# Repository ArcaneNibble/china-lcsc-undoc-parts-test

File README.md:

# China / LCSC poorly-documented parts tester PCB

## TM8211

This is a cheap I2S DAC that looks like it is intended for set-top-boxes. Allegedly, there is no minium clock speed. The goal is to determine if this is indeed true, in which case it can be bit-banged instead of doing proper I2S with a continuously-running clock. If it were to be the case, we would want to know the output impedance of the DAC.

### Status

I haven't managed to get this chip to output anything at all so far, even with a continuous clock. Further investigation needed.

## EA3058

This is a 4-channel buck converter. I wanted to characterize its performance in more detail than the few graphs in the datasheet.

### Status

The zero-load performance seems quite poor on the 1.2 V output. Further measurements have not been made yet.

## LGS5500

This is a LiPo charger and boost converter with automagic power path / load sharing. It appears to be perfectly-suited for battery-powered "maker" projects, especially ones that need 5 V and/or want to be able to push batteries to ~3 V rather than ~3.4 V (with an ultra-low-dropout regulator) or even higher voltages (using less and less of the battery capacity). Once again I wanted to characterize the performance in more detail than in the datasheet.

### Status

There is somewhat undesired behavior if there is no battery connected. Automagic power path / load sharing appears to work very well, but more measurements need to be made of whether spikes/dips happen. Needs more testing of the boost converter under load.

## APW7261

This is another LiPo charger and boost converter that is especially cheap. It was a bit unclear how (in)convenient it would be to use. It was also a test of using WLCSPs and pushing JLCPCB minimums.

### Status

This is clearly designed for legacy OTG, and it doesn't have the same type of automagic power path / load sharing as the previous part. It was assembled successfully without any issues.

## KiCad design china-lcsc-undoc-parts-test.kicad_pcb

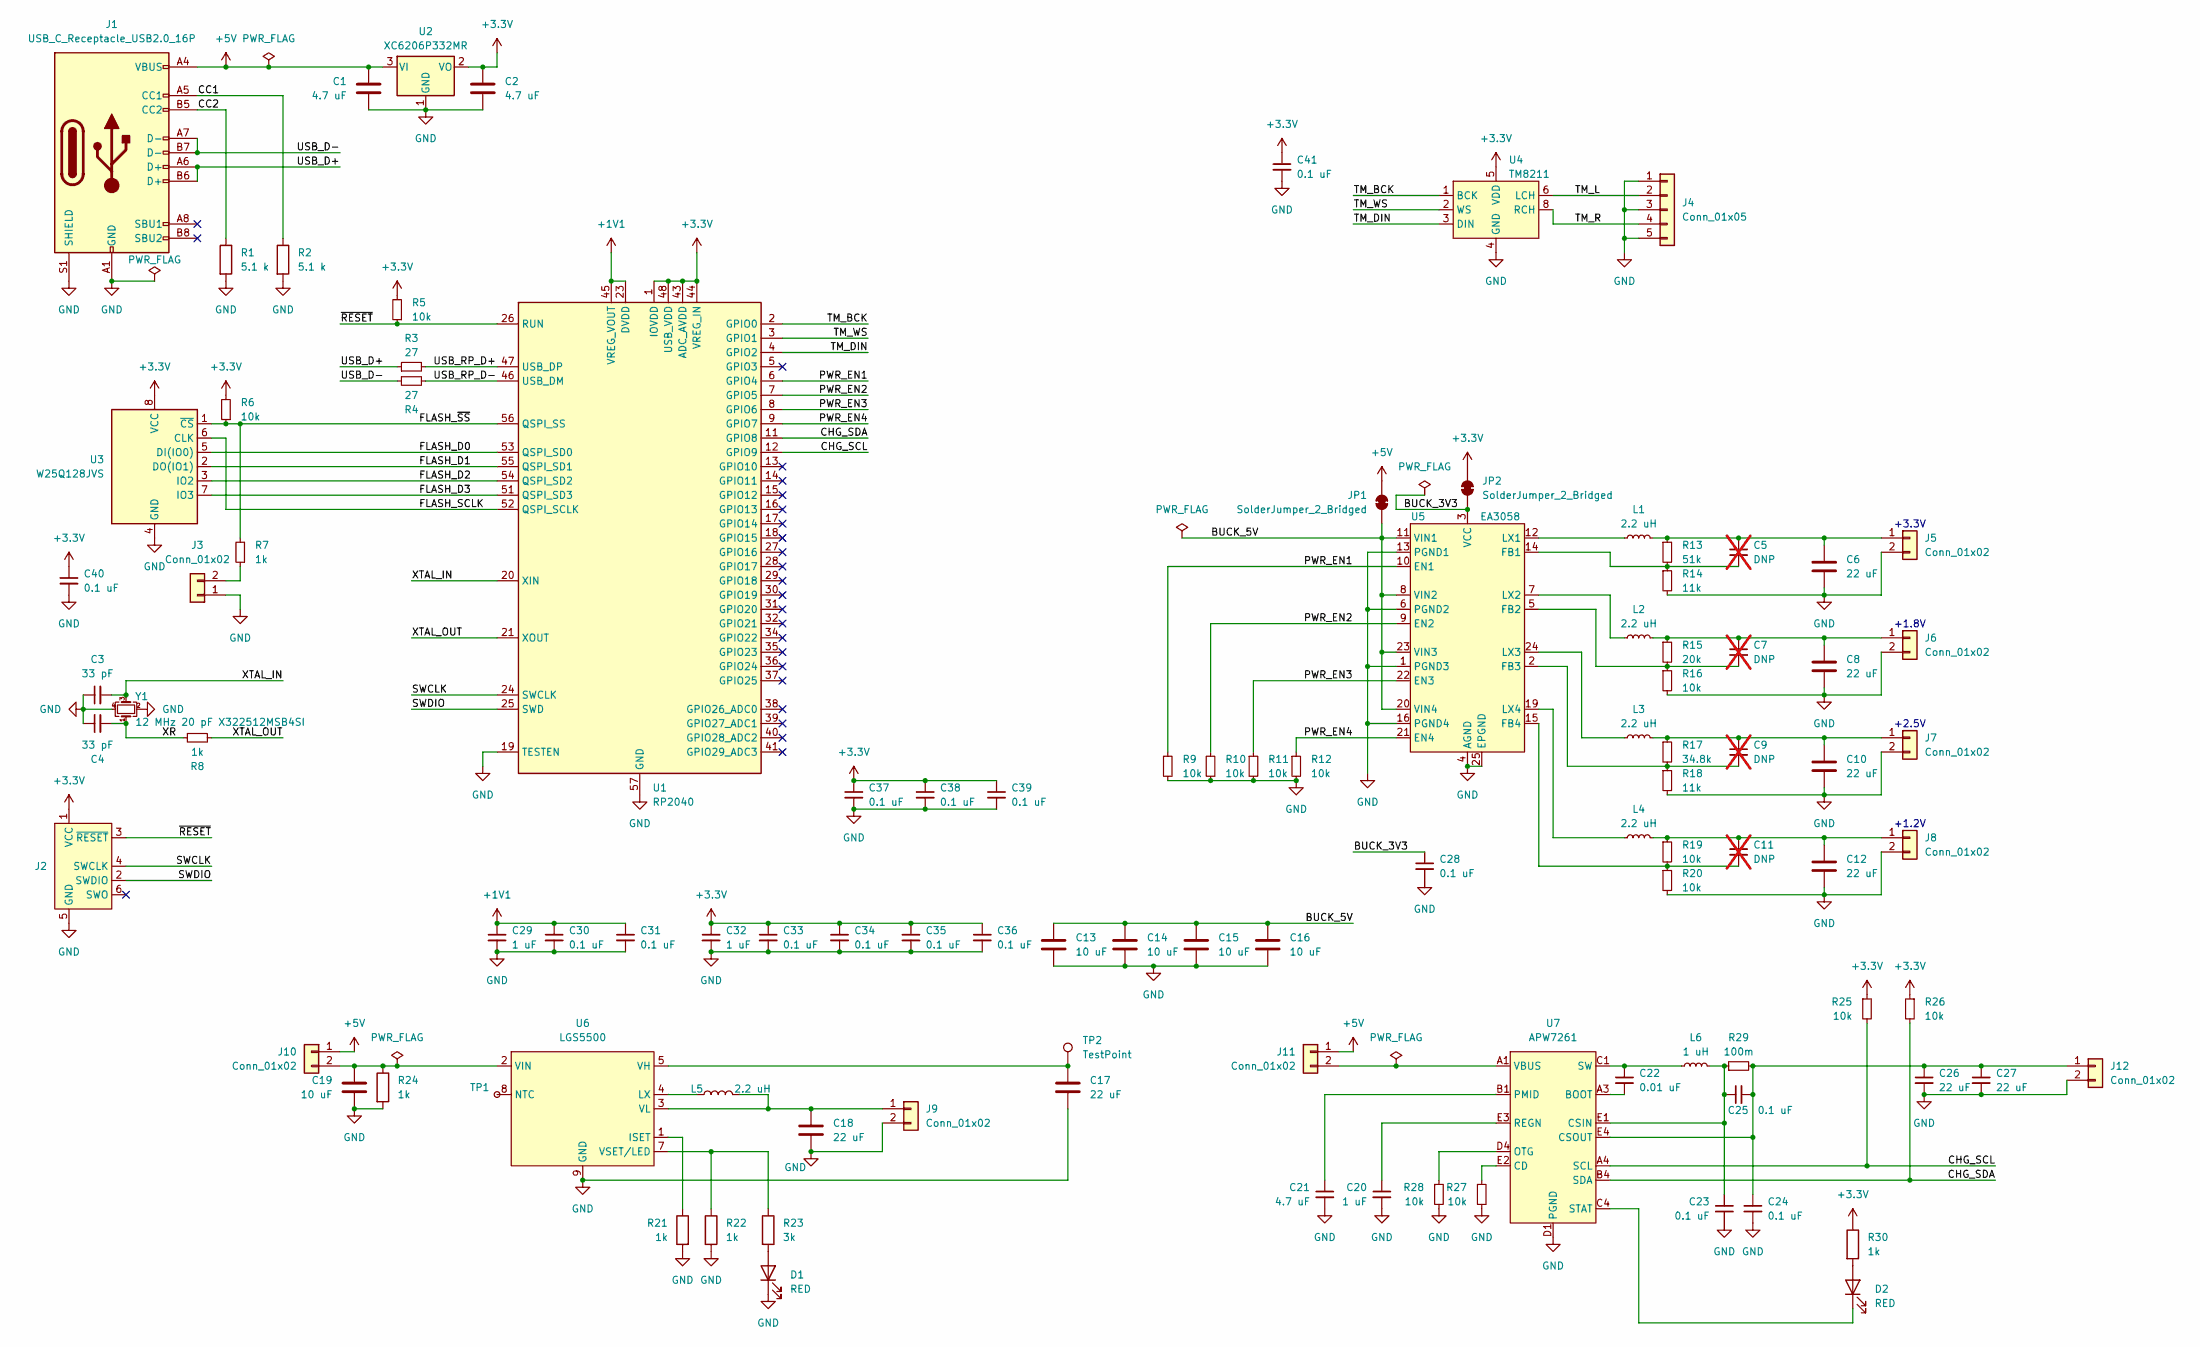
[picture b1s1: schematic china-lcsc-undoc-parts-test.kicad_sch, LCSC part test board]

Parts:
C1, C2, C21: 4.7 uF; C_0805_2012Metric; LCSC C1779
C3, C4: 33 pF; C_0402_1005Metric; LCSC C1562
C5, C7, C9, C11: DNP; C_0603_1608Metric; not fitted
C6, C8, C10, C12, C17, C18, C26, C27: 22 uF; C_1206_3216Metric; LCSC C12891
C13, C14, C15, C16, C19: 10 uF; C_1206_3216Metric; LCSC C13585
C20, C29, C32: 1 uF; C_0603_1608Metric; LCSC C15849
C22: 0.01 uF; C_0805_2012Metric; LCSC C1710
C23, C24, C25, C28, C30, C31, C33, C34, C35, C36, C37, C38, C39, C40, C41: 0.1 uF; C_0402_1005Metric; LCSC C1525
D1, D2: RED; LED_0603_1608Metric; LCSC C2286
J1: USB_C_Receptacle_USB2.0_16P; USB_C_Receptacle_GCT_USB4105-xx-A_16P_TopMnt_Horizontal; LCSC C2765186
J2: Conn_ARM_SWD_TagConnect_TC2030; Tag-Connect_TC2030-IDC-FP_2x03_P1.27mm_Vertical
J3, J5, J6, J7, J8, J10, J11: Conn_01x02; PinHeader_1x02_P2.54mm_Vertical
J4: Conn_01x05; PinHeader_1x05_P2.54mm_Vertical
J9, J12: Conn_01x02; JST_PH_B2B-PH-SM4-TB_1x02-1MP_P2.00mm_Vertical; LCSC C160352
JP1, JP2: SolderJumper_2_Bridged; SolderJumper-2_P1.3mm_Bridged_RoundedPad1.0x1.5mm
L1, L2, L3, L4, L5: 2.2 uH; L_Changjiang_FXL0420; LCSC C167206
L6: 1 uH; L_Changjiang_FXL0420; LCSC C167203
R1, R2: 5.1 k; R_0402_1005Metric; LCSC C25905
R3, R4: 27; R_0603_1608Metric; LCSC C25190
R5, R6, R9, R10, R11, R12, R16, R19, R20, R25, R26, R27, R28: 10k; R_0402_1005Metric; LCSC C25744
R7, R8, R21, R22, R24, R30: 1k; R_0402_1005Metric; LCSC C11702
R13: 51k; R_0402_1005Metric; LCSC C25794
R14, R18: 11k; R_0603_1608Metric; LCSC C25950
R15: 20k; R_0402_1005Metric; LCSC C25765
R17: 34.8k; R_0402_1005Metric; LCSC C47493
R23: 3k; R_0603_1608Metric; LCSC C4211
R29: 100m; R_1206_3216Metric; LCSC C188071
TP1: TestPoint_Small; PinHeader_1x01_P2.54mm_Vertical
TP2: TestPoint; PinHeader_1x01_P2.54mm_Vertical
U1: RP2040; QFN-56-1EP_7x7mm_P0.4mm_EP3.2x3.2mm; LCSC C2040
U2: XC6206P332MR; SOT-23-3; LCSC C5446
U3: W25Q128JVS; SOIC-8_5.23x5.23mm_P1.27mm; LCSC C97521
U4: TM8211; SOIC-8_3.9x4.9mm_P1.27mm; LCSC C92003
U5: EA3058; QFN-24-1EP_4x4mm_P0.5mm_EP2.6x2.6mm; LCSC C575412
U6: LGS5500; SOIC-8-1EP_3.9x4.9mm_P1.27mm_EP2.41x3.3mm; LCSC C5280699
U7: APW7261; WLCSP-24_1.76x2.03mm_P0.4mm; LCSC C691404
Y1: 12 MHz 20 pF X322512MSB4SI; Crystal_SMD_3225-4Pin_3.2x2.5mm; LCSC C9002

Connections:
+1V1: C29.1, C30.1, C31.1, U1.23 (DVDD), U1.45 (VREG_VOUT), U1.50 (DVDD)
+3.3V: C2.1, C32.1, C33.1, C34.1, C35.1, C36.1, C37.1, C38.1, C39.1, C40.1, C41.1, J2.1 (VCC), JP2.1 (A), R5.2, R6.2, R25.1, R26.1, R30.1, U1.1 (IOVDD), U1.10 (IOVDD), U1.22 (IOVDD), U1.33 (IOVDD), U1.42 (IOVDD), U1.43 (ADC_AVDD), U1.44 (VREG_IN), U1.48 (USB_VDD), U1.49 (IOVDD), U2.2 (VO), U3.8 (VCC), U4.5 (VDD)
+5V: C1.1, J1.A4 (VBUS), J1.A9 (VBUS), J1.B4 (VBUS), J1.B9 (VBUS), J10.1, J11.1, JP1.1 (A), U2.3 (VI)
/BUCK_3V3: C28.1, JP2.2 (B), U5.3 (VCC)
/BUCK_5V: C13.1, C14.1, C15.1, C16.1, JP1.2 (B), U5.8 (VIN2), U5.11 (VIN1), U5.20 (VIN4), U5.23 (VIN3)
/CC1: J1.A5 (CC1), R2.1
/CC2: J1.B5 (CC2), R1.1
/CHG_SCL: R25.2, U1.12 (GPIO9), U7.A4 (SCL)
/CHG_SDA: R26.2, U1.11 (GPIO8), U7.B4 (SDA)
/FLASH_D0: U1.53 (QSPI_SD0), U3.5 (DI(IO0))
/FLASH_D1: U1.55 (QSPI_SD1), U3.2 (DO(IO1))
/FLASH_D2: U1.54 (QSPI_SD2), U3.3 (IO2)
/FLASH_D3: U1.51 (QSPI_SD3), U3.7 (IO3)
/FLASH_SCLK: U1.52 (QSPI_SCLK), U3.6 (CLK)
/FLASH_~SS: R6.1, R7.2, U1.56 (QSPI_SS), U3.1 (~CS)
/PWR_EN1: R9.1, U1.6 (GPIO4), U5.10 (EN1)
/PWR_EN2: R10.1, U1.7 (GPIO5), U5.9 (EN2)
/PWR_EN3: R11.1, U1.8 (GPIO6), U5.22 (EN3)
/PWR_EN4: R12.1, U1.9 (GPIO7), U5.21 (EN4)
/SWCLK: J2.4 (SWCLK), U1.24 (SWCLK)
/SWDIO: J2.2 (SWDIO), U1.25 (SWD)
/TM_BCK: U1.2 (GPIO0), U4.1 (BCK)
/TM_DIN: U1.4 (GPIO2), U4.3 (DIN)
/TM_L: J4.2, U4.6 (LCH)
/TM_R: J4.4, U4.8 (RCH)
/TM_WS: U1.3 (GPIO1), U4.2 (WS)
/USB_D+: J1.A6 (D+), J1.B6 (D+), R3.1
/USB_D-: J1.A7 (D-), J1.B7 (D-), R4.1
/USB_RP_D+: R3.2, U1.47 (USB_DP)
/USB_RP_D-: R4.2, U1.46 (USB_DM)
/XR: C4.2, R8.1, Y1.1
/XTAL_IN: C3.2, U1.20 (XIN), Y1.3
/XTAL_OUT: R8.2, U1.21 (XOUT)
/~RESET: J2.3 (~RESET), R5.1, U1.26 (RUN)
GND: C1.2, C2.2, C3.1, C4.1, C6.2, C8.2, C10.2, C12.2, C13.2, C14.2, C15.2, C16.2, C17.2, C18.2, C19.2, C20.2, C21.2, C23.2, C24.2, C26.2, C27.2, C28.2, C29.2, C30.2, C31.2, C32.2, C33.2, C34.2, C35.2, C36.2, C37.2, C38.2, C39.2, C40.2, C41.2, D1.1 (K), J1.A1 (GND), J1.A12 (GND), J1.B1 (GND), J1.B12 (GND), J1.S1 (SHIELD), J2.5 (GND), J3.1, J4.1, J4.3, J4.5, J5.2, J6.2, J7.2, J8.2, J9.2, J12.2, R1.2, R2.2, R9.2, R10.2, R11.2, R12.2, R14.2, R16.2, R18.2, R20.2, R21.2, R22.2, R24.2, R27.2, R28.2, U1.19 (TESTEN), U1.57 (GND), U2.1 (GND), U3.4 (GND), U4.4 (GND), U5.1 (PGND3), U5.4 (AGND), U5.6 (PGND2), U5.13 (PGND1), U5.16 (PGND4), U5.25 (EPGND), U6.9 (GND), U7.D1 (PGND), U7.D2 (PGND), U7.D3 (PGND), Y1.2, Y1.4
unnamed: C21.1, U7.B1 (PMID), U7.B2 (PMID), U7.B3 (PMID)
unnamed: C22.1, L6.1, U7.C1 (SW), U7.C2 (SW), U7.C3 (SW)
unnamed: D1.2 (A), R23.2
unnamed: D2.2 (A), R30.2
unnamed: D2.1 (K), U7.C4 (STAT)
unnamed: J3.2, R7.1
unnamed: C5.1, C6.1, J5.1, L1.2, R13.1
unnamed: C7.1, C8.1, J6.1, L2.2, R15.1
unnamed: C9.1, C10.1, J7.1, L3.2, R17.1
unnamed: C11.1, C12.1, J8.1, L4.2, R19.1
unnamed: C18.1, J9.1, L5.2, U6.3 (VL)
unnamed: C19.1, J10.2, R24.1, U6.2 (VIN)
unnamed: J11.2, U7.A1 (VBUS), U7.A2 (VBUS)
unnamed: C24.1, C25.2, C26.1, C27.1, J12.1, R29.2, U7.E4 (CSOUT)
unnamed: C5.2, R13.2, R14.1, U5.14 (FB1)
unnamed: C7.2, R15.2, R16.1, U5.5 (FB2)
unnamed: C9.2, R17.2, R18.1, U5.2 (FB3)
unnamed: C11.2, R19.2, R20.1, U5.15 (FB4)
unnamed: L1.1, U5.12 (LX1)
unnamed: L2.1, U5.7 (LX2)
unnamed: L3.1, U5.24 (LX3)
unnamed: L4.1, U5.19 (LX4)
unnamed: R21.1, U6.1 (ISET)
unnamed: L5.1, U6.4 (LX)
unnamed: TP1.1, U6.8 (NTC)
unnamed: C17.1, TP2.1, U6.5 (VH)
unnamed: R22.1, R23.1, U6.7 (VSET/LED)
unnamed: C22.2, U7.A3 (BOOT)
unnamed: R27.1, U7.E2 (CD)
unnamed: C23.1, C25.1, L6.2, R29.1, U7.E1 (CSIN)
unnamed: R28.1, U7.D4 (OTG)
unnamed: C20.1, U7.E3 (REGN)

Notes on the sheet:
+1.2V
+2.5V
+1.8V
+3.3V

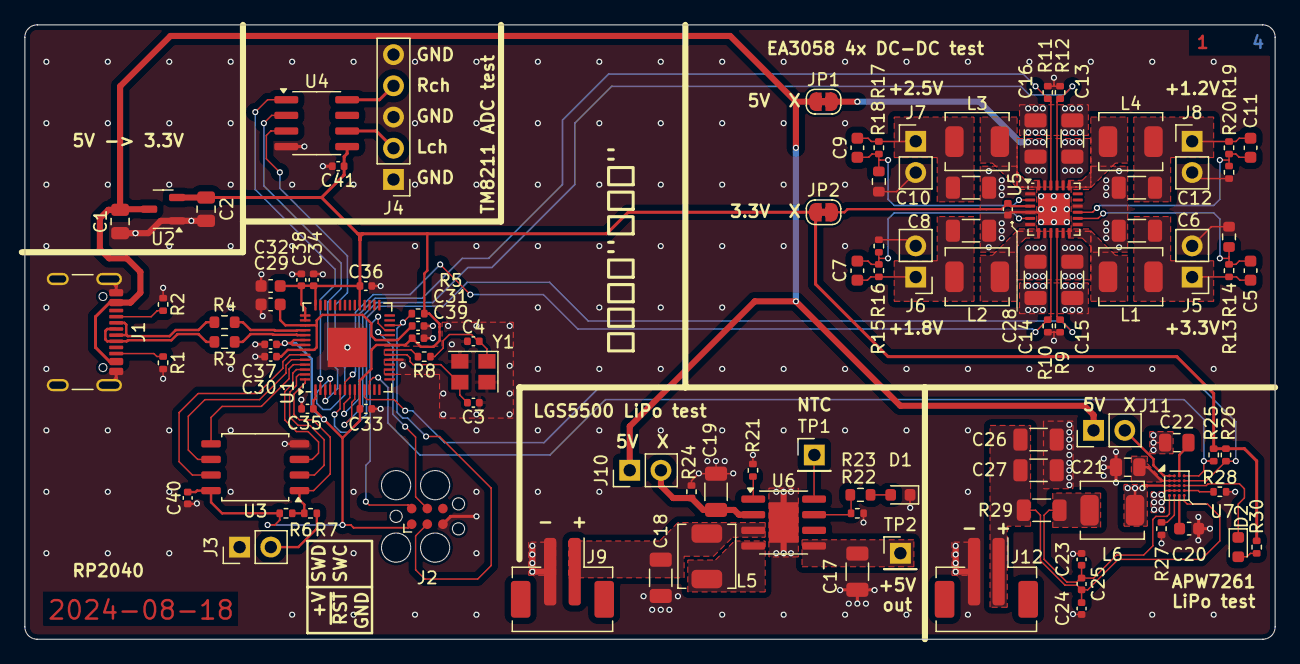
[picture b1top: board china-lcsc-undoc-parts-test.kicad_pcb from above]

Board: 4 copper layers, 101.8 x 50.0 mm, 103 parts (0 on the bottom side), 67 nets.

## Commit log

2024-09-03 Initial reimport commit
2024-09-03 Add readme and license
2024-09-03 reword note about lipos
